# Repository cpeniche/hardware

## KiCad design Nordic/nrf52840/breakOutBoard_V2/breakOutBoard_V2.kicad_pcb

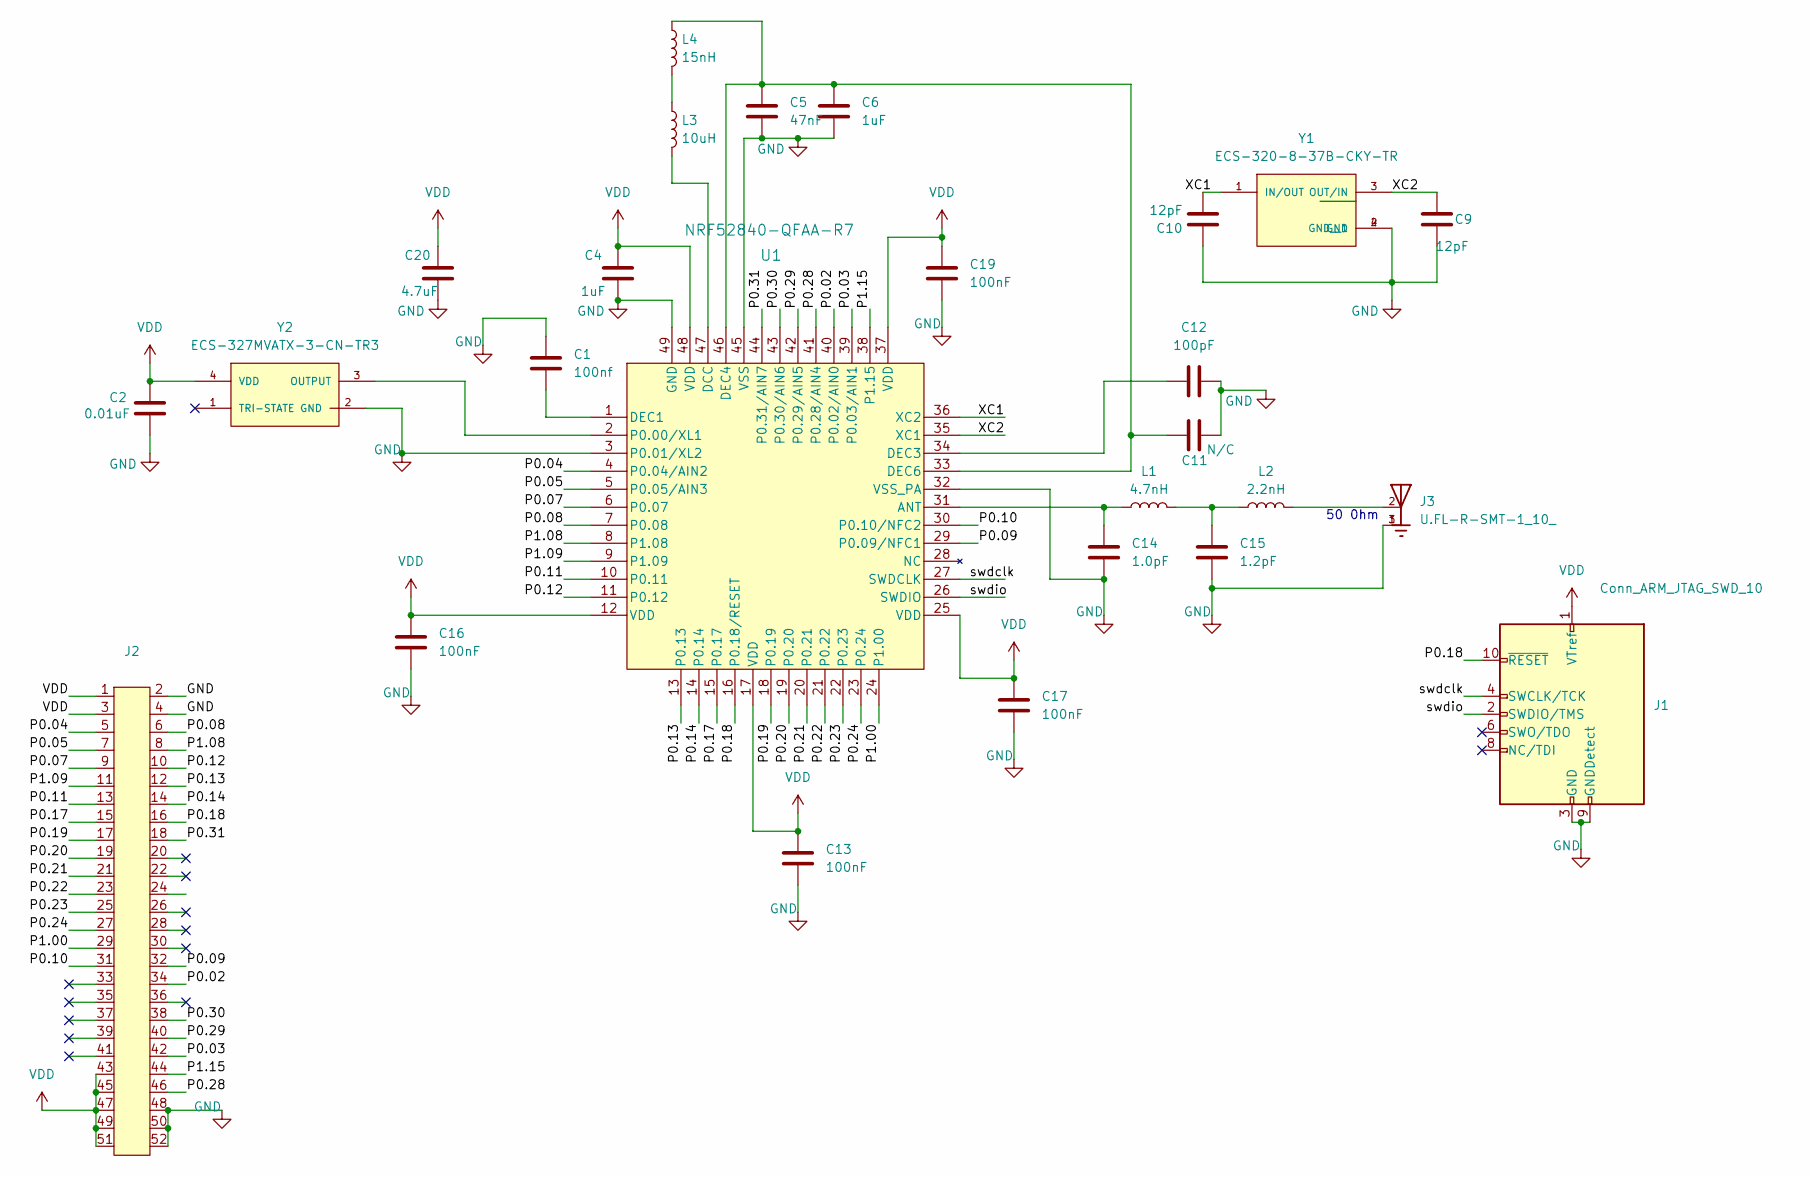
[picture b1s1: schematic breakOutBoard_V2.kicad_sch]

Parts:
C1: 100nf; C_0603_1608Metric_Pad1.08x0.95mm_HandSolder
C2: 0.01uF; C_0603_1608Metric_Pad1.08x0.95mm_HandSolder
C4, C6: 1uF; C_0603_1608Metric_Pad1.08x0.95mm_HandSolder
C5: 47nF; C_0603_1608Metric_Pad1.08x0.95mm_HandSolder
C9, C10: 12pF; C_0603_1608Metric_Pad1.08x0.95mm_HandSolder
C11: N/C; C_0603_1608Metric_Pad1.08x0.95mm_HandSolder
C12: 100pF; C_0603_1608Metric_Pad1.08x0.95mm_HandSolder
C13, C16, C17, C19: 100nF; C_0603_1608Metric_Pad1.08x0.95mm_HandSolder
C14: 1.0pF; C_0402_1005Metric_Pad0.74x0.62mm_HandSolder
C15: 1.2pF; C_0402_1005Metric_Pad0.74x0.62mm_HandSolder
C20: 4.7uF; C_0603_1608Metric_Pad1.08x0.95mm_HandSolder
J1: Conn_ARM_JTAG_SWD_10; PinHeader_2x05_P1.27mm_Vertical
J2: Mini PCI express Half
J3: U.FL-R-SMT-1_10_; HRS_U.FL-R-SMT-1_10_; MPN U.FL-R-SMT-1(10)
L1: 4.7nH; L_0402_1005Metric_Pad0.77x0.64mm_HandSolder
L2: 2.2nH; L_0402_1005Metric_Pad0.77x0.64mm_HandSolder
L3: 10uH; L_0603_1608Metric_Pad1.05x0.95mm_HandSolder
L4: 15nH; L_0603_1608Metric_Pad1.05x0.95mm_HandSolder
U1: NRF52840-QFAA-R7; QFN-48-1EP_6x6mm_P0.4mm_EP4.6x4.6mm_ThermalVias
Y1: ECS-320-8-37B-CKY-TR; XTAL_ECS-160-9-37-CKM-TR; PARTREV 2017
Y2: ECS-327MVATX-3-CN-TR3; OSC_ECS-2333-160-BN-TR; PARTREV N/A

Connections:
/P0.02: J2.34, U1.40 (P0.02/AIN0)
/P0.03: J2.42, U1.39 (P0.03/AIN1)
/P0.04: J2.5, U1.4 (P0.04/AIN2)
/P0.05: J2.7, U1.5 (P0.05/AIN3)
/P0.07: J2.9, U1.6 (P0.07)
/P0.08: J2.6, U1.7 (P0.08)
/P0.09: J2.32, U1.29 (P0.09/NFC1)
/P0.10: J2.31, U1.30 (P0.10/NFC2)
/P0.11: J2.13, U1.10 (P0.11)
/P0.12: J2.10, U1.11 (P0.12)
/P0.13: J2.12, U1.13 (P0.13)
/P0.14: J2.14, U1.14 (P0.14)
/P0.17: J2.15, U1.15 (P0.17)
/P0.18: J1.10 (~RESET), J2.16, U1.16 (P0.18/RESET)
/P0.19: J2.17, U1.18 (P0.19)
/P0.20: J2.19, U1.19 (P0.20)
/P0.21: J2.21, U1.20 (P0.21)
/P0.22: J2.23, U1.21 (P0.22)
/P0.23: J2.25, U1.22 (P0.23)
/P0.24: J2.27, U1.23 (P0.24)
/P0.28: J2.46, U1.41 (P0.28/AIN4)
/P0.29: J2.40, U1.42 (P0.29/AIN5)
/P0.30: J2.38, U1.43 (P0.30/AIN6)
/P0.31: J2.18, U1.44 (P0.31/AIN7)
/P1.00: J2.29, U1.24 (P1.00)
/P1.08: J2.8, U1.8 (P1.08)
/P1.09: J2.11, U1.9 (P1.09)
/P1.15: J2.44, U1.38 (P1.15)
/XC1: C10.2, U1.36 (XC2), Y1.1 (IN/OUT)
/XC2: C9.2, U1.35 (XC1), Y1.3 (OUT/IN)
/swdclk: J1.4 (SWCLK/TCK), U1.27 (SWDCLK)
/swdio: J1.2 (SWDIO/TMS), U1.26 (SWDIO)
GND: C1.1, C2.2, C4.2, C5.2, C6.2, C9.1, C10.1, C11.2, C12.2, C13.2, C14.2, C15.2, C16.2, C17.2, C19.2, C20.2, J1.3 (GND), J1.5 (GND), J1.9 (GNDDetect), J2.2, J2.4, J2.48, J2.50, J2.52, J3.1, J3.3, U1.3 (P0.01/XL2), U1.32 (VSS_PA), U1.45 (VSS), U1.49 (GND), Y1.2 (GND), Y1.4 (GND__1), Y2.2 (GND)
unnamed: C15.1, L1.2, L2.1
unnamed: J3.2, L2.2
unnamed: L3.1, L4.2
unnamed: C14.1, L1.1, U1.31 (ANT)
unnamed: L3.2, U1.47 (DCC)
unnamed: C1.2, U1.1 (DEC1)
unnamed: C12.1, U1.34 (DEC3)
unnamed: C5.1, C6.1, C11.1, L4.1, U1.33 (DEC6), U1.46 (DEC4)
unnamed: U1.2 (P0.00/XL1), Y2.3 (OUTPUT)
VDD: C2.1, C4.1, C13.1, C16.1, C17.1, C19.1, C20.1, J1.1 (VTref), J2.1, J2.3, J2.43, J2.45, J2.47, J2.49, J2.51, U1.12 (VDD), U1.17 (VDD), U1.25 (VDD), U1.37 (VDD), U1.48 (VDD), Y2.4 (VDD)

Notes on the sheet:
50 0hm

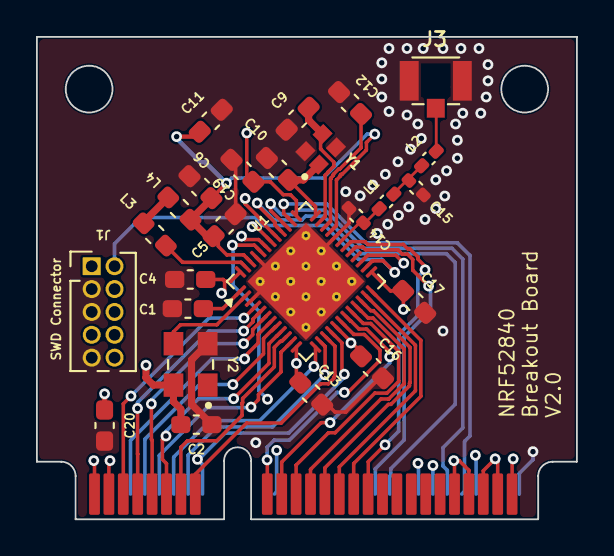
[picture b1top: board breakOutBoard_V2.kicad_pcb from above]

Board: 4 copper layers, 30.0 x 26.8 mm, 26 parts (0 on the bottom side), 43 nets.

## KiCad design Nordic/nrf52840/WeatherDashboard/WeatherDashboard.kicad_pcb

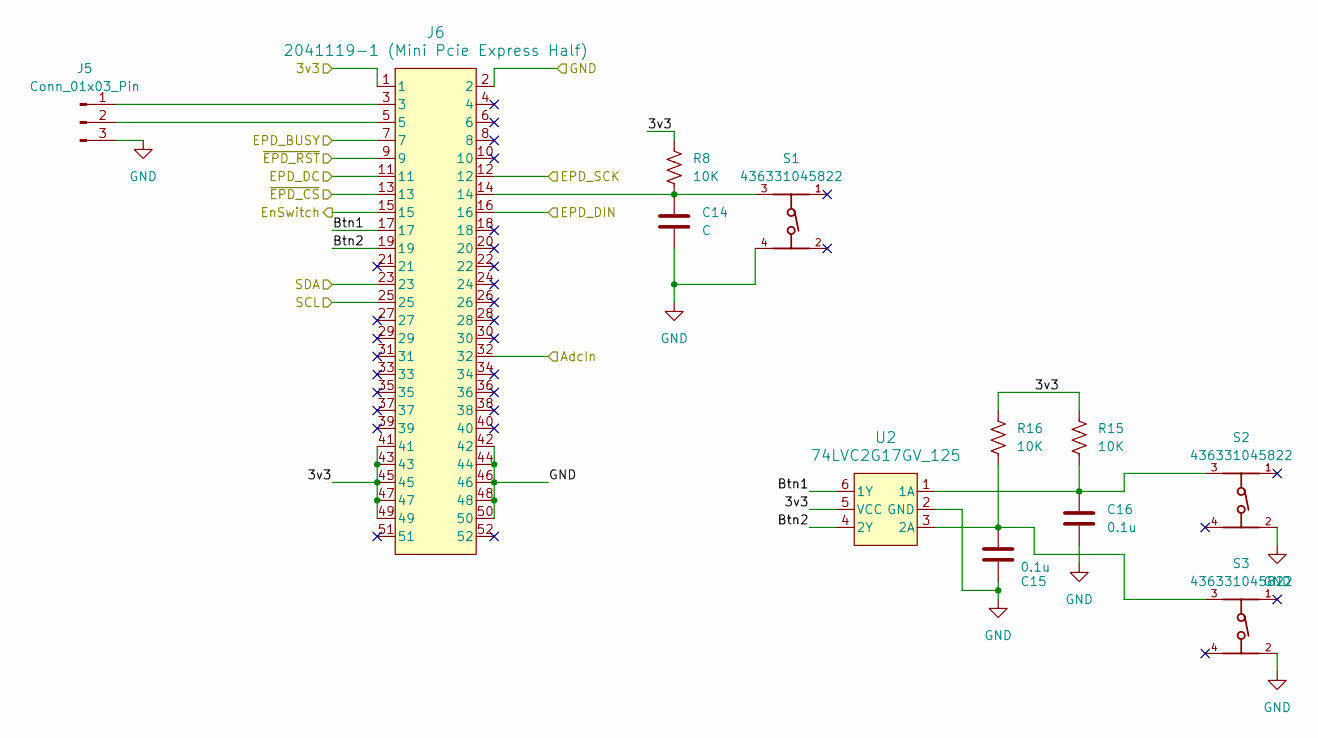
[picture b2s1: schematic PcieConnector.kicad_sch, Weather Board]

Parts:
C14: C; C_0805_2012Metric_Pad1.18x1.45mm_HandSolder
C15, C16: 0.1u; C_0402_1005Metric_Pad0.74x0.62mm_HandSolder
J5: Conn_01x03_Pin; PinSocket_1x03_P2.54mm_Vertical
J6: 2041119-1 (Mini Pcie Express Half); CONN_2041119-1_TEC
R8, R15, R16: 10K; R_0402_1005Metric_Pad0.72x0.64mm_HandSolder
S1, S2, S3: 436331045822; 4363X10458XX
U2: 74LVC2G17GV_125; SC-74_TSOP6_NEX

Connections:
/Display/3v3: J6.1, J6.41, J6.43, J6.45, J6.47, J6.49, R8.1, R15.1, R16.1, U2.5 (VCC); also elsewhere on the board
/Display/EPD_BUSY: J6.7; also elsewhere on the board
/Display/EPD_DC: J6.11; also elsewhere on the board
/Display/EPD_DIN: J6.16; also elsewhere on the board
/Display/EPD_SCK: J6.12; also elsewhere on the board
/Display/TSCL: J6.25; also elsewhere on the board
/Display/TSDA: J6.23; also elsewhere on the board
/Display/~EPD_CS: J6.13; also elsewhere on the board
/Display/~EPD_RST: J6.9; also elsewhere on the board
/Pcie Connector/AdcIn: J6.32; also elsewhere on the board
/Pcie Connector/Btn1: J6.17, U2.6 (1Y)
/Pcie Connector/Btn2: J6.19, U2.4 (2Y)
/Pcie Connector/EnSwitch: J6.15; also elsewhere on the board
GND: C14.2, C15.2, C16.2, J5.3, J6.2, J6.42, J6.44, J6.46, J6.48, J6.50, S1.4, S2.2, S3.2, U2.2 (GND); also elsewhere on the board
unnamed: C14.1, J6.14, R8.2, S1.3
unnamed: J5.1, J6.3
unnamed: J5.2, J6.5
unnamed: C16.1, R15.2, S2.3, U2.1 (1A)
unnamed: C15.1, R16.2, S3.3, U2.3 (2A)

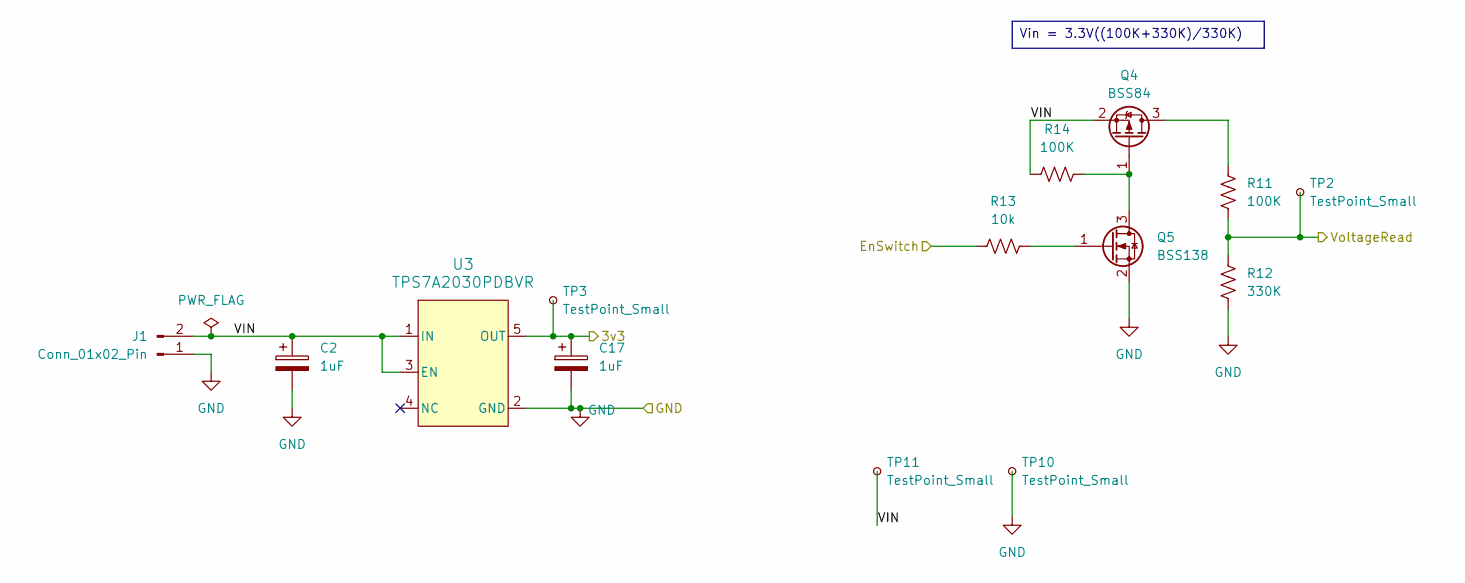
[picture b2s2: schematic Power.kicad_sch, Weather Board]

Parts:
C2, C17: 1uF; CP_EIA-3216-12_Kemet-S_HandSolder
J1: Conn_01x02_Pin; PinHeader_1x02_P2.54mm_Vertical
Q4: BSS84; SOT-23
Q5: BSS138; SOT-23
R11, R14: 100K; R_0402_1005Metric_Pad0.72x0.64mm_HandSolder
R12: 330K; R_0402_1005Metric_Pad0.72x0.64mm_HandSolder
R13: 10k; R_0402_1005Metric_Pad0.72x0.64mm_HandSolder
TP2, TP3, TP10, TP11: TestPoint_Small; TestPoint_Pad_1.0x1.0mm
U3: TPS7A2030PDBVR; DBV0005A-IPC_C

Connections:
/Display/3v3: C17.1, TP3.1, U3.5 (OUT); also elsewhere on the board
/Pcie Connector/AdcIn: R11.2, R12.1, TP2.1; also elsewhere on the board
/Pcie Connector/EnSwitch: R13.1; also elsewhere on the board
/Power/VIN: C2.1, J1.2, Q4.2 (S), R14.1, TP11.1, U3.1 (IN), U3.3 (EN)
GND: C2.2, C17.2, J1.1, Q5.2 (S), R12.2, TP10.1, U3.2 (GND); also elsewhere on the board
unnamed: Q4.3 (D), R11.1
unnamed: Q4.1 (G), Q5.3 (D), R14.2
unnamed: Q5.1 (G), R13.2

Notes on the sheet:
Vin = 3.3V((100K+330K)/330K)

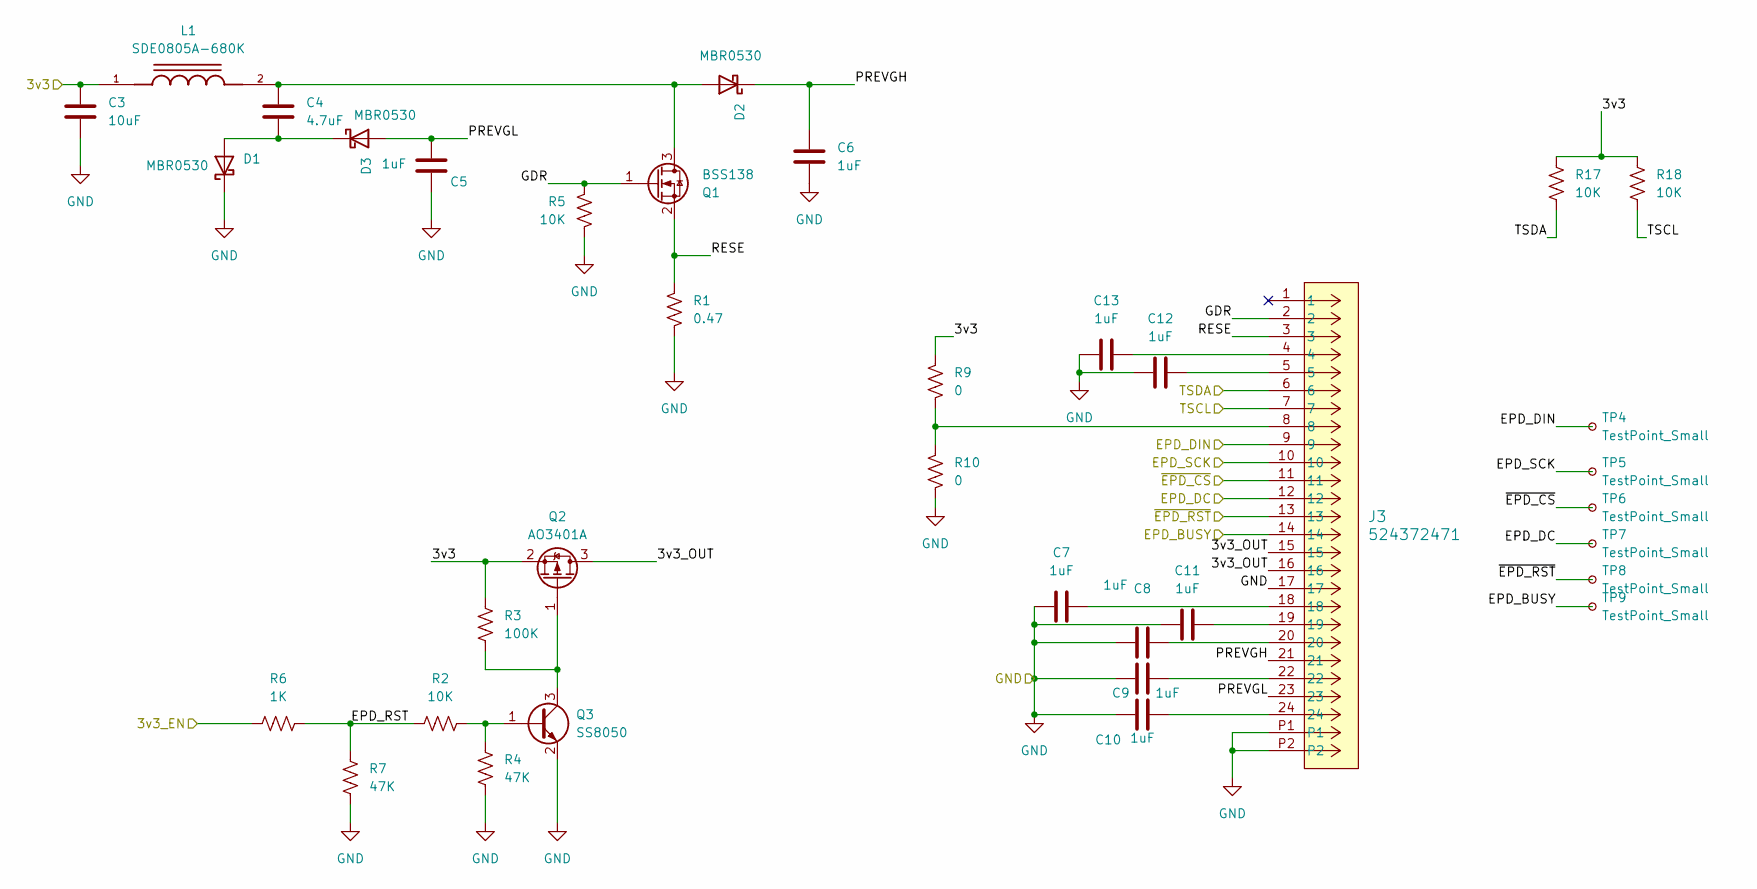
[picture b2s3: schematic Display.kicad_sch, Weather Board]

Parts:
C3: 10uF; C_0402_1005Metric_Pad0.74x0.62mm_HandSolder
C4: 4.7uF; C_0402_1005Metric_Pad0.74x0.62mm_HandSolder
C5, C6, C7, C8, C9, C10, C11, C12, C13: 1uF; C_0402_1005Metric_Pad0.74x0.62mm_HandSolder
D1, D2, D3: MBR0530; D_SOD-123
J3: 524372471; CON_524372471_MOL
L1: SDE0805A-680K; IND_SDE0805A-680K; PARTREV 11/19
Q1: BSS138; SOT-23_Handsoldering
Q2: AO3401A; SOT-23
Q3: SS8050; SOT-23_Handsoldering
R1: 0.47; R_0402_1005Metric_Pad0.72x0.64mm_HandSolder
R2, R5, R17, R18: 10K; R_0402_1005Metric_Pad0.72x0.64mm_HandSolder
R3: 100K; R_0402_1005Metric_Pad0.72x0.64mm_HandSolder
R4, R7: 47K; R_0402_1005Metric_Pad0.72x0.64mm_HandSolder
R6: 1K; R_0402_1005Metric_Pad0.72x0.64mm_HandSolder
R9, R10: 0; R_0402_1005Metric_Pad0.72x0.64mm_HandSolder
TP4, TP5, TP6, TP7, TP8, TP9: TestPoint_Small; TestPoint_Pad_1.0x1.0mm

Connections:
/Display/3v3: C3.1, L1.1, Q2.2 (S), R3.1, R6.2, R9.1, R17.2, R18.2; also elsewhere on the board
/Display/3v3_OUT: J3.15, J3.16, Q2.3 (D)
/Display/EPD_BUSY: J3.14, TP9.1; also elsewhere on the board
/Display/EPD_DC: J3.12, TP7.1; also elsewhere on the board
/Display/EPD_DIN: J3.9, TP4.1; also elsewhere on the board
/Display/EPD_RST: R2.1, R6.1, R7.2
/Display/EPD_SCK: J3.10, TP5.1; also elsewhere on the board
/Display/GDR: J3.2, Q1.1 (G), R5.2
/Display/PREVGH: C6.1, D2.1 (K), J3.21
/Display/PREVGL: C5.1, D3.2 (A), J3.23
/Display/RESE: J3.3, Q1.2 (S), R1.1
/Display/TSCL: J3.7, R18.1; also elsewhere on the board
/Display/TSDA: J3.6, R17.1; also elsewhere on the board
/Display/~EPD_CS: J3.11, TP6.1; also elsewhere on the board
/Display/~EPD_RST: J3.13, TP8.1; also elsewhere on the board
GND: C3.2, C5.2, C6.2, C7.1, C8.1, C9.1, C10.1, C11.1, C12.1, C13.1, D1.1 (K), J3.17, J3.P1, J3.P2, Q3.2 (E), R1.2, R4.2, R5.1, R7.1, R10.2; also elsewhere on the board
unnamed: C7.2, J3.18
unnamed: C8.2, J3.20
unnamed: C9.2, J3.22
unnamed: C10.2, J3.24
unnamed: C11.2, J3.19
unnamed: C12.2, J3.5
unnamed: C13.2, J3.4
unnamed: C4.2, D1.2 (A), D3.1 (K)
unnamed: C4.1, D2.2 (A), L1.2, Q1.3 (D)
unnamed: J3.8, R9.2, R10.1
unnamed: Q2.1 (G), Q3.3 (C), R3.2
unnamed: Q3.1 (B), R2.2, R4.1

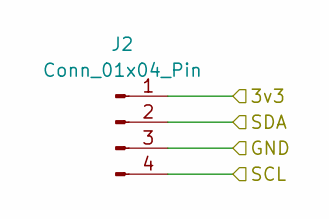
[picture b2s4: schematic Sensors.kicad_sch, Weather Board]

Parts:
J2: Conn_01x04_Pin; PinHeader_1x04_P2.54mm_Vertical

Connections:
/Display/3v3: J2.1; also elsewhere on the board
/Display/TSCL: J2.4; also elsewhere on the board
/Display/TSDA: J2.2; also elsewhere on the board
GND: J2.3; also elsewhere on the board

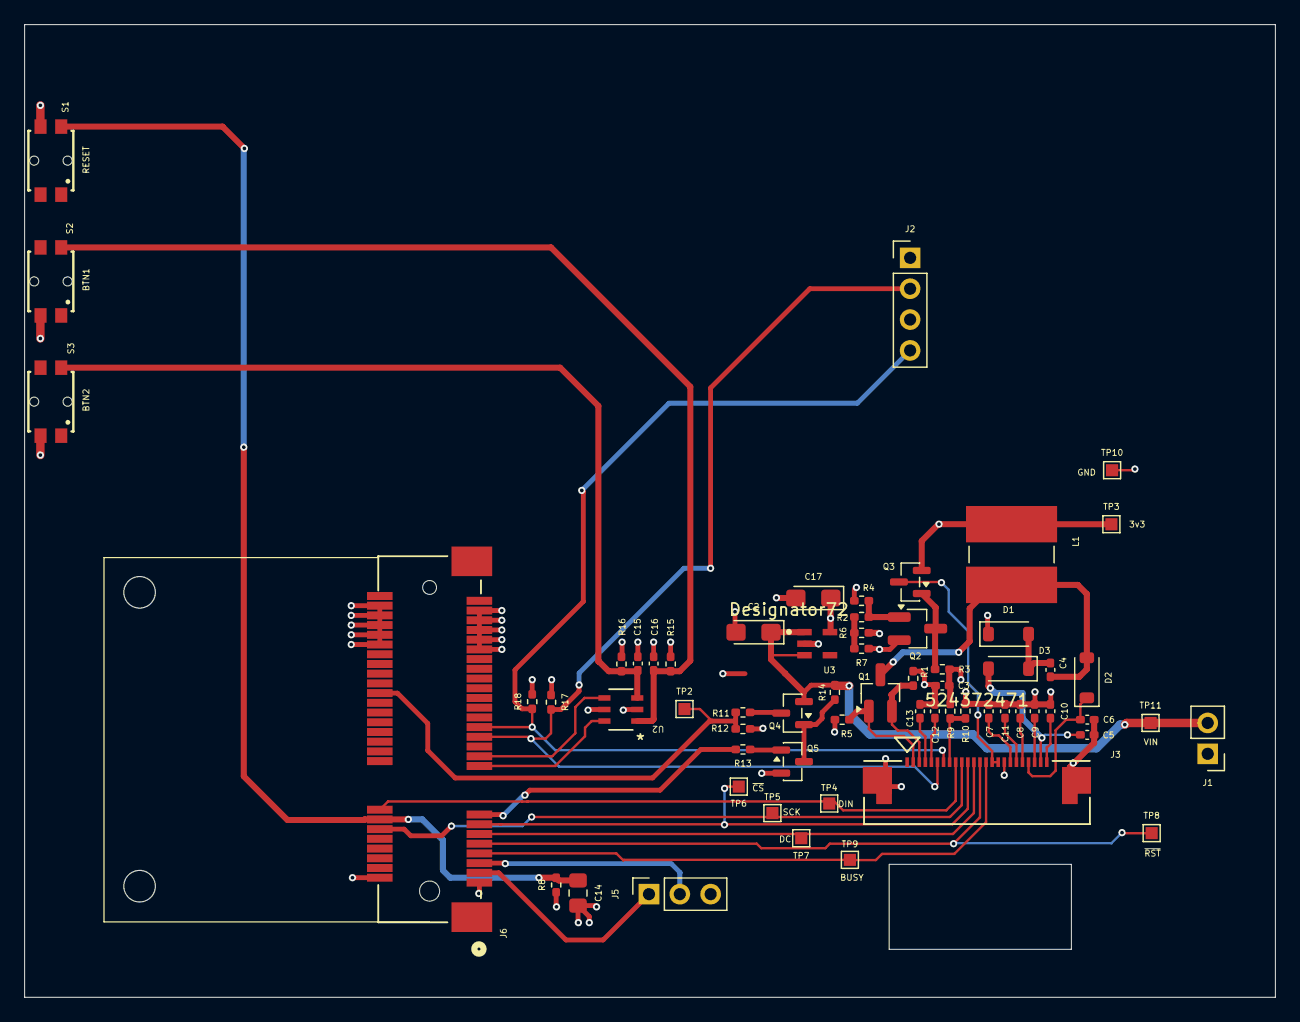
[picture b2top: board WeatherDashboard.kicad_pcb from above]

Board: 4 copper layers, 103.0 x 80.1 mm, 63 parts (0 on the bottom side), 41 nets.

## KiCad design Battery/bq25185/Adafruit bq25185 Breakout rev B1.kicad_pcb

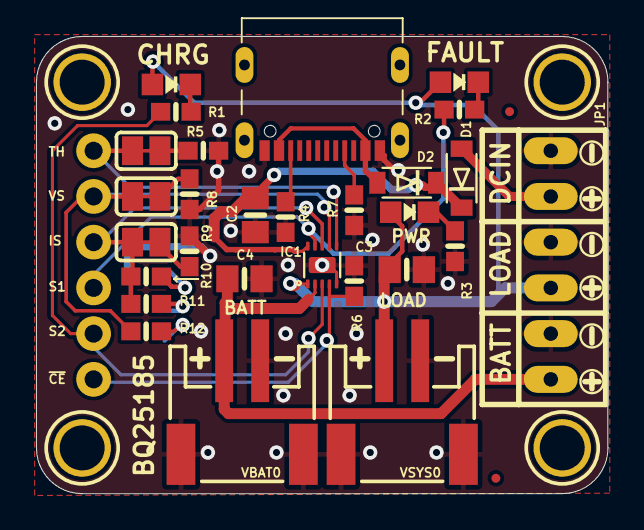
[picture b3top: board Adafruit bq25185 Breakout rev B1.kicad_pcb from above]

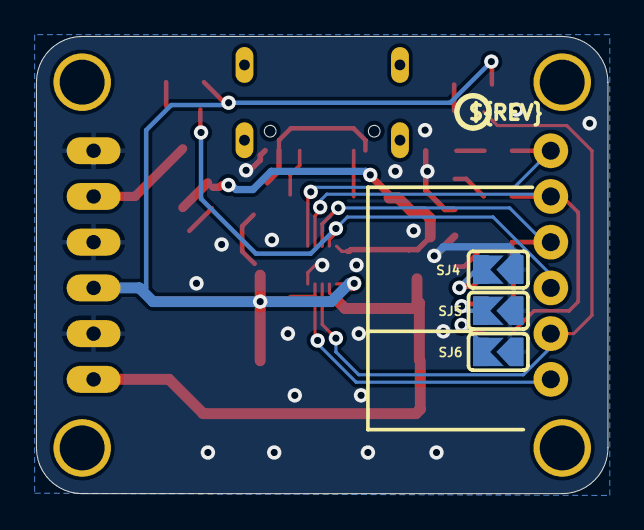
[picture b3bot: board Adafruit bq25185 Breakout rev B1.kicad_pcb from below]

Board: 2 copper layers, 31.8 x 25.4 mm, 68 parts (12 on the bottom side), 23 nets.

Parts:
C2, C3, C4: 22uF; 0805-NO
CHG0: ORANGE; CHIPLED_0805_NOOUTLINE
D1, D2: MBRX120; SOD-123FL
FAULT0: RED; CHIPLED_0805_NOOUTLINE
IC1: BQ25185; WSON10
JP1: HEADER-1X6OVALWAVE; 1X06_OVALWAVE
JP2, JP4: FIDUCIAL1.5X3; FIDUCIAL_0.5MM
JP7: HEADER-1X676MIL; 1X06_ROUND_76
PLABEL0: PLABEL0
PLABEL1: PLABEL1
PLABEL2: PLABEL2
PLABEL3: PLABEL3
PLABEL4: PLABEL4
PLABEL5: PLABEL5
PLABEL6: PLABEL6
PLABEL7: PLABEL7
PLABEL8: PLABEL8
PLABEL9: PLABEL9
PLABEL10: PLABEL10
PLABEL11: PLABEL11
PLABEL12: PLABEL12
PLABEL13: PLABEL13
PLABEL14: PLABEL14
PLABEL15: PLABEL15
PLABEL16: PLABEL16
PLABEL18: PLABEL18
PLABEL19: PLABEL19
PLABEL20: PLABEL20
PLABEL21: PLABEL21
PLABEL22: PLABEL22
PLABEL23: PLABEL23
R1, R2, R3: 1K; 0603-NO
R4, R7, R12: 5.1K; 0603-NO
R5, R6: 10K; 0603-NO
R8: 13K; 0603-NO
R9: 600; 0603-NO
R10: 300; 0603-NO
R11: 1200; 0603-NO
SJ1, SJ2, SJ3: SOLDERJUMPER_CLOSED; SOLDERJUMPER_CLOSEDWIRE
SJ4, SJ5, SJ6: SOLDERJUMPER; SOLDERJUMPER_ARROW_NOPASTE
U$11, U$16, U$18, U$19: MOUNTINGHOLE2.5; MOUNTINGHOLE_2.5_PLATED
U$23, U$27, U$28: SYMBOL_PLUS
U$24, U$25, U$26: SYMBOL_MINUS
U$47: PCBFEAT-REV-040
VBAT0: JST2PH; JSTPH2_BATT
VSYS0: JST2PH; JSTPH2_BATT
VSYSOK0: GREEN; CHIPLED_0805_NOOUTLINE
X3: USBC; USB_C_CUSB31-CFM2AX-01-X

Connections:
5.0V: C3.1, CHG0.A, FAULT0.A, IC1.1 (VSYS), JP1.4, VSYS0.2, VSYSOK0.A
/ISET: IC1.8 (ISET), JP7.3, R10.1, R11.1, SJ3.1
/STAT1: IC1.9 (STAT1), JP7.4, R2.1
/STAT2: IC1.3 (STAT2), JP7.5, R1.1
/THERM: IC1.6 (TS/MR), JP7.1, SJ1.2
/USB: D2.A, X3.A4B9 (VBUS), X3.B4A9 (VBUS)
/VSET: IC1.7 (VSET), JP7.2, R12.1, SJ2.2
//CE: IC1.4 (/CE), JP7.6, R6.2
GND: C2.2, C3.2, C4.2, IC1.5 (GND), IC1.PAD (GND), JP1.1, JP1.3, JP1.5, R3.2, R4.1, R5.1, R6.1, R7.1, R8.2, R9.2, SJ4.1, SJ5.1, SJ6.1, VBAT0.1, VBAT0.NC1, VBAT0.NC2, VSYS0.1, VSYS0.NC1, VSYS0.NC2, X3.A1B12 (GND), X3.B1A12 (GND)
unnamed: CHG0.C, R1.2
unnamed: D1.A, JP1.2
unnamed: FAULT0.C, R2.2
unnamed: R3.1, VSYSOK0.C
unnamed: R5.2, SJ1.1
unnamed: R8.1, SJ2.1
unnamed: R9.1, SJ3.2
unnamed: R10.2, SJ4.2
unnamed: R11.2, SJ5.2
unnamed: R12.2, SJ6.2
unnamed: R7.2, X3.A5 (CC1)
unnamed: R4.2, X3.B5 (CC2)
VBAT: C4.1, IC1.2 (VBAT), JP1.6, VBAT0.2
VBUS: C2.1, D1.C, D2.C, IC1.10 (VBUS)

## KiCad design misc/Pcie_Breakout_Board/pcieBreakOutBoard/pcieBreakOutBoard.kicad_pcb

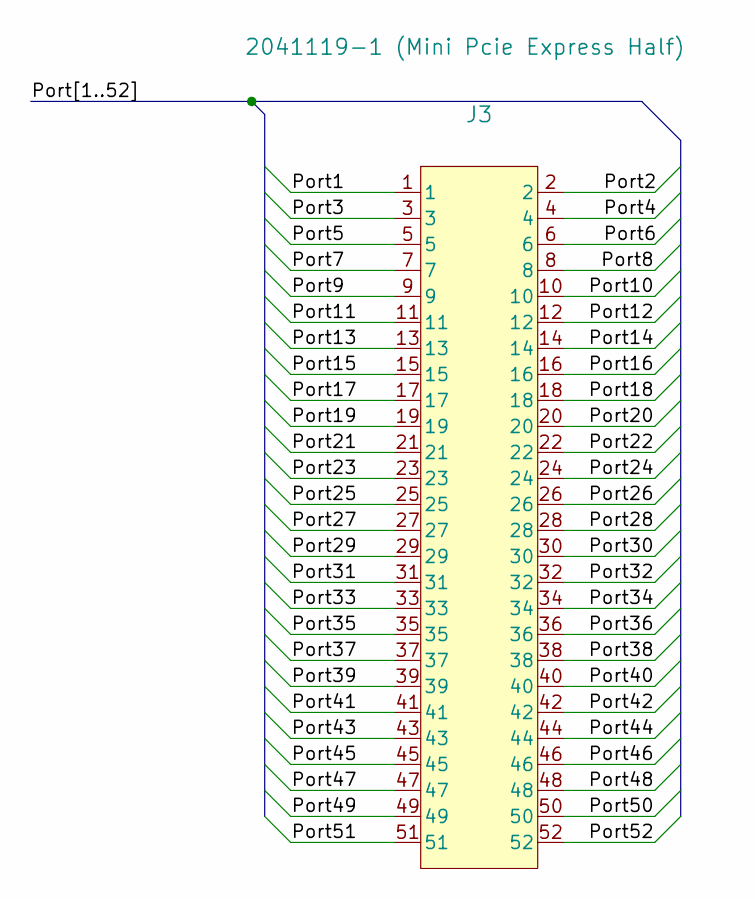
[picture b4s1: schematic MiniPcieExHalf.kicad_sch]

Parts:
J3: 2041119-1 (Mini Pcie Express Half); BUS_PCI_Express_Mini_Half

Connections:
/MiniPcieExHalf/Port1: J3.1
/MiniPcieExHalf/Port2: J3.2
/MiniPcieExHalf/Port3: J3.3
/MiniPcieExHalf/Port4: J3.4
/MiniPcieExHalf/Port5: J3.5
/MiniPcieExHalf/Port6: J3.6
/MiniPcieExHalf/Port7: J3.7
/MiniPcieExHalf/Port8: J3.8
/MiniPcieExHalf/Port9: J3.9
/MiniPcieExHalf/Port10: J3.10
/MiniPcieExHalf/Port11: J3.11
/MiniPcieExHalf/Port12: J3.12
/MiniPcieExHalf/Port13: J3.13
/MiniPcieExHalf/Port14: J3.14
/MiniPcieExHalf/Port15: J3.15
/MiniPcieExHalf/Port16: J3.16
/MiniPcieExHalf/Port17: J3.17
/MiniPcieExHalf/Port18: J3.18
/MiniPcieExHalf/Port19: J3.19
/MiniPcieExHalf/Port20: J3.20
/MiniPcieExHalf/Port21: J3.21
/MiniPcieExHalf/Port22: J3.22
/MiniPcieExHalf/Port23: J3.23
/MiniPcieExHalf/Port24: J3.24
/MiniPcieExHalf/Port25: J3.25
/MiniPcieExHalf/Port26: J3.26
/MiniPcieExHalf/Port27: J3.27
/MiniPcieExHalf/Port28: J3.28
/MiniPcieExHalf/Port29: J3.29
/MiniPcieExHalf/Port30: J3.30
/MiniPcieExHalf/Port31: J3.31
/MiniPcieExHalf/Port32: J3.32
/MiniPcieExHalf/Port33: J3.33
/MiniPcieExHalf/Port34: J3.34
/MiniPcieExHalf/Port35: J3.35
/MiniPcieExHalf/Port36: J3.36
/MiniPcieExHalf/Port37: J3.37
/MiniPcieExHalf/Port38: J3.38
/MiniPcieExHalf/Port39: J3.39
/MiniPcieExHalf/Port40: J3.40
/MiniPcieExHalf/Port41: J3.41
/MiniPcieExHalf/Port42: J3.42
/MiniPcieExHalf/Port43: J3.43
/MiniPcieExHalf/Port44: J3.44
/MiniPcieExHalf/Port45: J3.45
/MiniPcieExHalf/Port46: J3.46
/MiniPcieExHalf/Port47: J3.47
/MiniPcieExHalf/Port48: J3.48
/MiniPcieExHalf/Port49: J3.49
/MiniPcieExHalf/Port50: J3.50
/MiniPcieExHalf/Port51: J3.51
/MiniPcieExHalf/Port52: J3.52

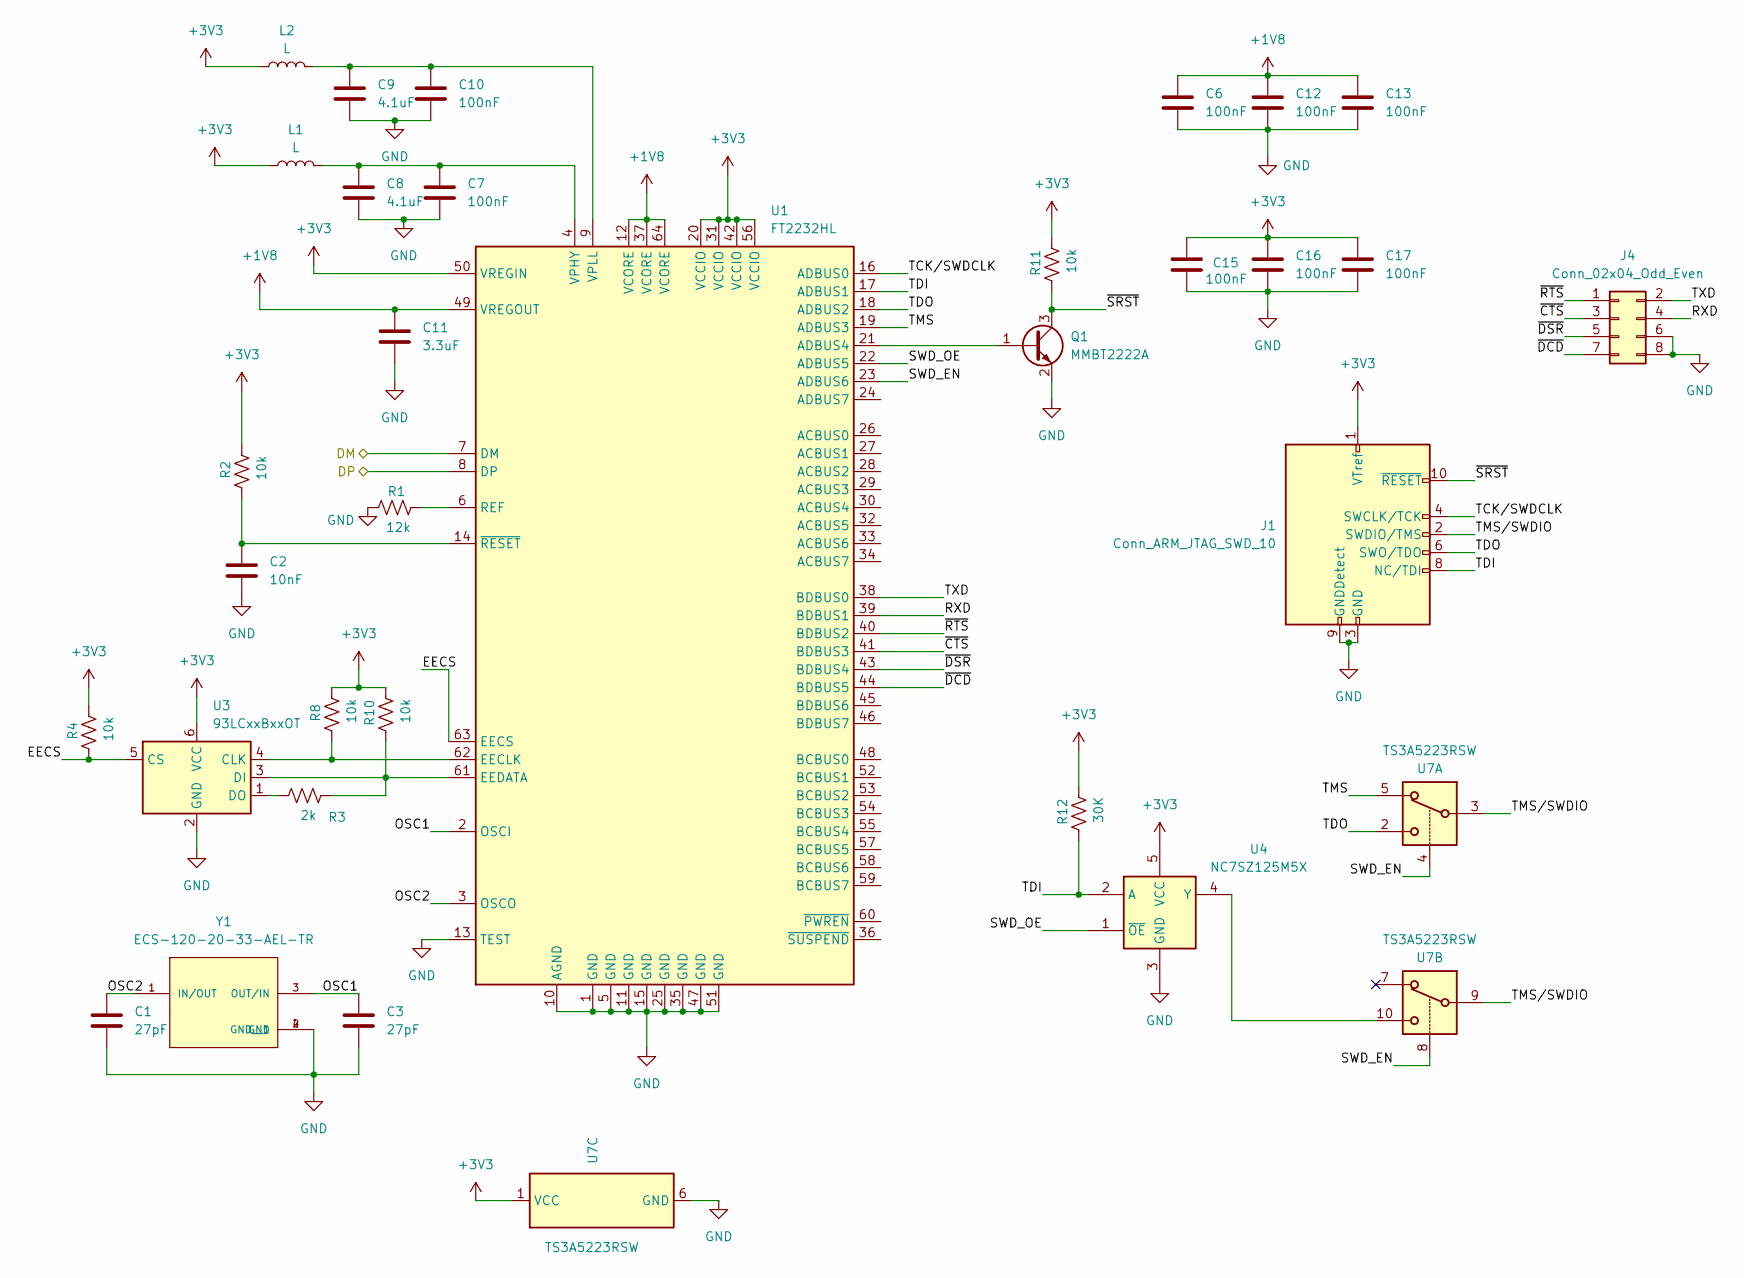
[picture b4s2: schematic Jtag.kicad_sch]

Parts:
C1, C3: 27pF; C_0402_1005Metric_Pad0.74x0.62mm_HandSolder
C2: 10nF; C_0402_1005Metric_Pad0.74x0.62mm_HandSolder
C6, C7, C10, C12, C13, C15, C16, C17: 100nF; C_0402_1005Metric_Pad0.74x0.62mm_HandSolder
C8, C9: 4.1uF; C_0402_1005Metric_Pad0.74x0.62mm_HandSolder
C11: 3.3uF; C_0402_1005Metric_Pad0.74x0.62mm_HandSolder
J1: Conn_ARM_JTAG_SWD_10; PinHeader_2x05_P1.27mm_Vertical
J4: Conn_02x04_Odd_Even; PinHeader_2x04_P2.54mm_Vertical
L1, L2: L; L_0402_1005Metric_Pad0.77x0.64mm_HandSolder
Q1: MMBT2222A; SOT-23_Handsoldering
R1: 12k; R_0402_1005Metric_Pad0.72x0.64mm_HandSolder
R2, R4, R8, R10, R11: 10k; R_0402_1005Metric_Pad0.72x0.64mm_HandSolder
R3: 2k; R_0402_1005Metric_Pad0.72x0.64mm_HandSolder
R12: 30K; R_0402_1005Metric_Pad0.72x0.64mm_HandSolder
U1: FT2232HL; LQFP-64_10x10mm_P0.5mm
U3: 93LCxxBxxOT; SOT-23-6
U4: NC7SZ125M5X; SOT-23-5
U7: TS3A5223RSW; Texas_RSW0010A_UQFN-10_1.4x1.8mm_P0.4mm
Y1: ECS-120-20-33-AEL-TR; XTAL_ECS-120-20-33-AEL-TR

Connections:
+1V8: C6.1, C11.1, C12.1, C13.1, U1.12 (VCORE), U1.37 (VCORE), U1.49 (VREGOUT), U1.64 (VCORE)
+3V3: C15.1, C16.1, C17.1, J1.1 (VTref), L1.1, L2.1, R2.2, R4.2, R8.2, R10.2, R11.2, R12.2, U1.20 (VCCIO), U1.31 (VCCIO), U1.42 (VCCIO), U1.50 (VREGIN), U1.56 (VCCIO), U3.6 (VCC), U4.5 (VCC), U7.1 (VCC); also elsewhere on the board
/Jtag/DM: U1.7 (DM)
/Jtag/DP: U1.8 (DP)
/Jtag/EECS: R4.1, U1.63 (EECS), U3.5 (CS)
/Jtag/OSC1: C3.1, U1.2 (OSCI), Y1.3 (OUT/IN)
/Jtag/OSC2: C1.1, U1.3 (OSCO), Y1.1 (IN/OUT)
/Jtag/RXD: J4.4, U1.39 (BDBUS1)
/Jtag/SWD_EN: U1.23 (ADBUS6), U7.4, U7.8
/Jtag/SWD_OE: U1.22 (ADBUS5), U4.1 (~OE)
/Jtag/TCK/SWDCLK: J1.4 (SWCLK/TCK), U1.16 (ADBUS0)
/Jtag/TDI: J1.8 (NC/TDI), R12.1, U1.17 (ADBUS1), U4.2 (A)
/Jtag/TDO: J1.6 (SWO/TDO), U1.18 (ADBUS2), U7.2
/Jtag/TMS: U1.19 (ADBUS3), U7.5
/Jtag/TMS/SWDIO: J1.2 (SWDIO/TMS), U7.3, U7.9
/Jtag/TXD: J4.2, U1.38 (BDBUS0)
/Jtag/~CTS: J4.3, U1.41 (BDBUS3)
/Jtag/~DCD: J4.7, U1.44 (BDBUS5)
/Jtag/~DSR: J4.5, U1.43 (BDBUS4)
/Jtag/~RTS: J4.1, U1.40 (BDBUS2)
/Jtag/~SRST: J1.10 (~RESET), Q1.3 (C), R11.1
GND: C1.2, C2.2, C3.2, C6.2, C7.2, C8.2, C9.2, C10.2, C11.2, C12.2, C13.2, C15.2, C16.2, C17.2, J1.3 (GND), J1.5 (GND), J1.9 (GNDDetect), J4.6, J4.8, Q1.2 (E), R1.1, U1.1 (GND), U1.5 (GND), U1.10 (AGND), U1.11 (GND), U1.13 (TEST), U1.15 (GND), U1.25 (GND), U1.35 (GND), U1.47 (GND), U1.51 (GND), U3.2 (GND), U4.3 (GND), U7.6 (GND), Y1.2 (GND), Y1.4 (GND__1); also elsewhere on the board
unnamed: Q1.1 (B), U1.21 (ADBUS4)
unnamed: R8.1, U1.62 (EECLK), U3.4 (CLK)
unnamed: R3.2, R10.1, U1.61 (EEDATA), U3.3 (DI)
unnamed: R1.2, U1.6 (REF)
unnamed: C7.1, C8.1, L1.2, U1.4 (VPHY)
unnamed: C9.1, C10.1, L2.2, U1.9 (VPLL)
unnamed: C2.1, R2.1, U1.14 (~RESET)
unnamed: R3.1, U3.1 (DO)
unnamed: U4.4 (Y), U7.10

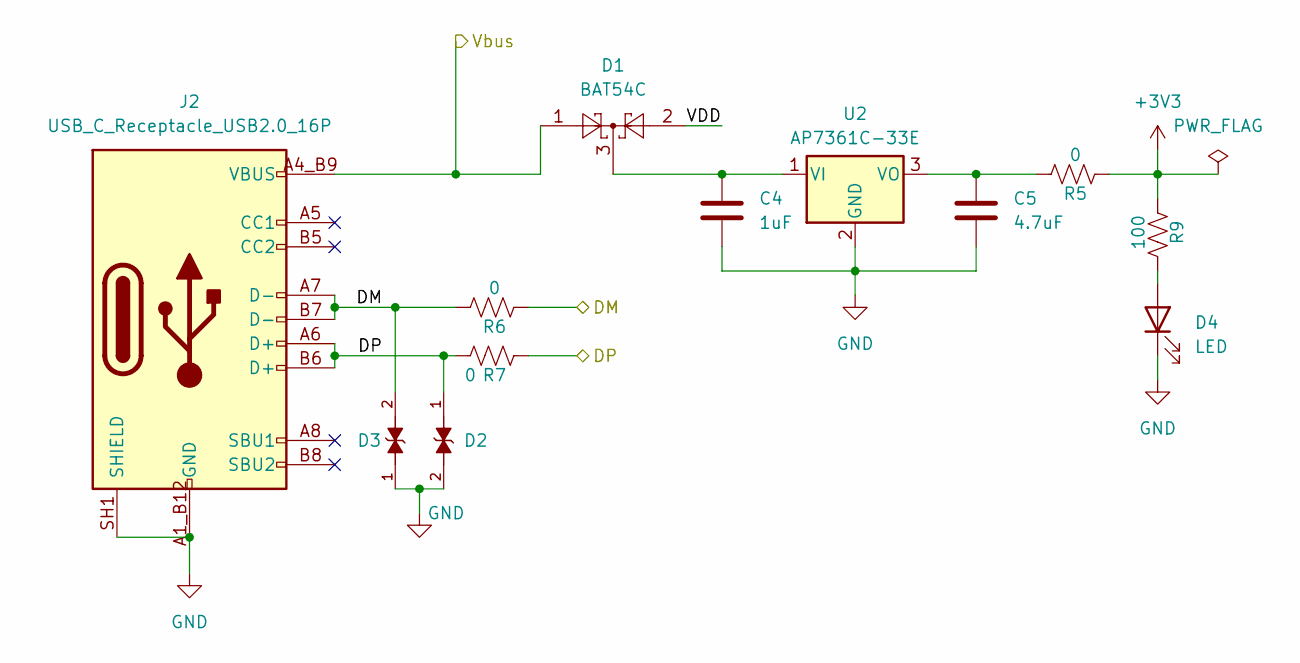
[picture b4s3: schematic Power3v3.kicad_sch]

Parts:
C4: 1uF; C_0402_1005Metric_Pad0.74x0.62mm_HandSolder
C5: 4.7uF; C_0402_1005Metric_Pad0.74x0.62mm_HandSolder
D1: BAT54C; SOT-23
D2, D3: PGB1010603NR; DIOC1608X36N
D4: LED; LED_0402_1005Metric
J2: USB_C_Receptacle_USB2.0_16P; AMPHENOL_GSB1C41110SSHR; PARTREV AX1
R5, R6, R7: 0; R_0402_1005Metric_Pad0.72x0.64mm_HandSolder
R9: 100; R_0402_1005Metric_Pad0.72x0.64mm_HandSolder
U2: AP7361C-33E; SOT-223-3_TabPin2

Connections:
+3V3: R5.2, R9.2; also elsewhere on the board
/Power/DM: D3.2, J2.A7 (D-), J2.B7 (D-), R6.1, R6.2
/Power/DP: D2.1, J2.A6 (D+), J2.B6 (D+), R7.1, R7.2
/Power/VDD: D1.2
/Power/Vbus: D1.1, J2.A4_B9 (VBUS), J2.B4_A9 (VBUS)
GND: C4.2, C5.2, D2.2, D3.1, D4.1 (K), J2.A1_B12 (GND), J2.B1_A12 (GND), J2.SH1 (SHIELD), U2.2 (GND); also elsewhere on the board
unnamed: D4.2 (A), R9.1
unnamed: C4.1, D1.3, U2.1 (VI)
unnamed: C5.1, R5.1, U2.3 (VO)
